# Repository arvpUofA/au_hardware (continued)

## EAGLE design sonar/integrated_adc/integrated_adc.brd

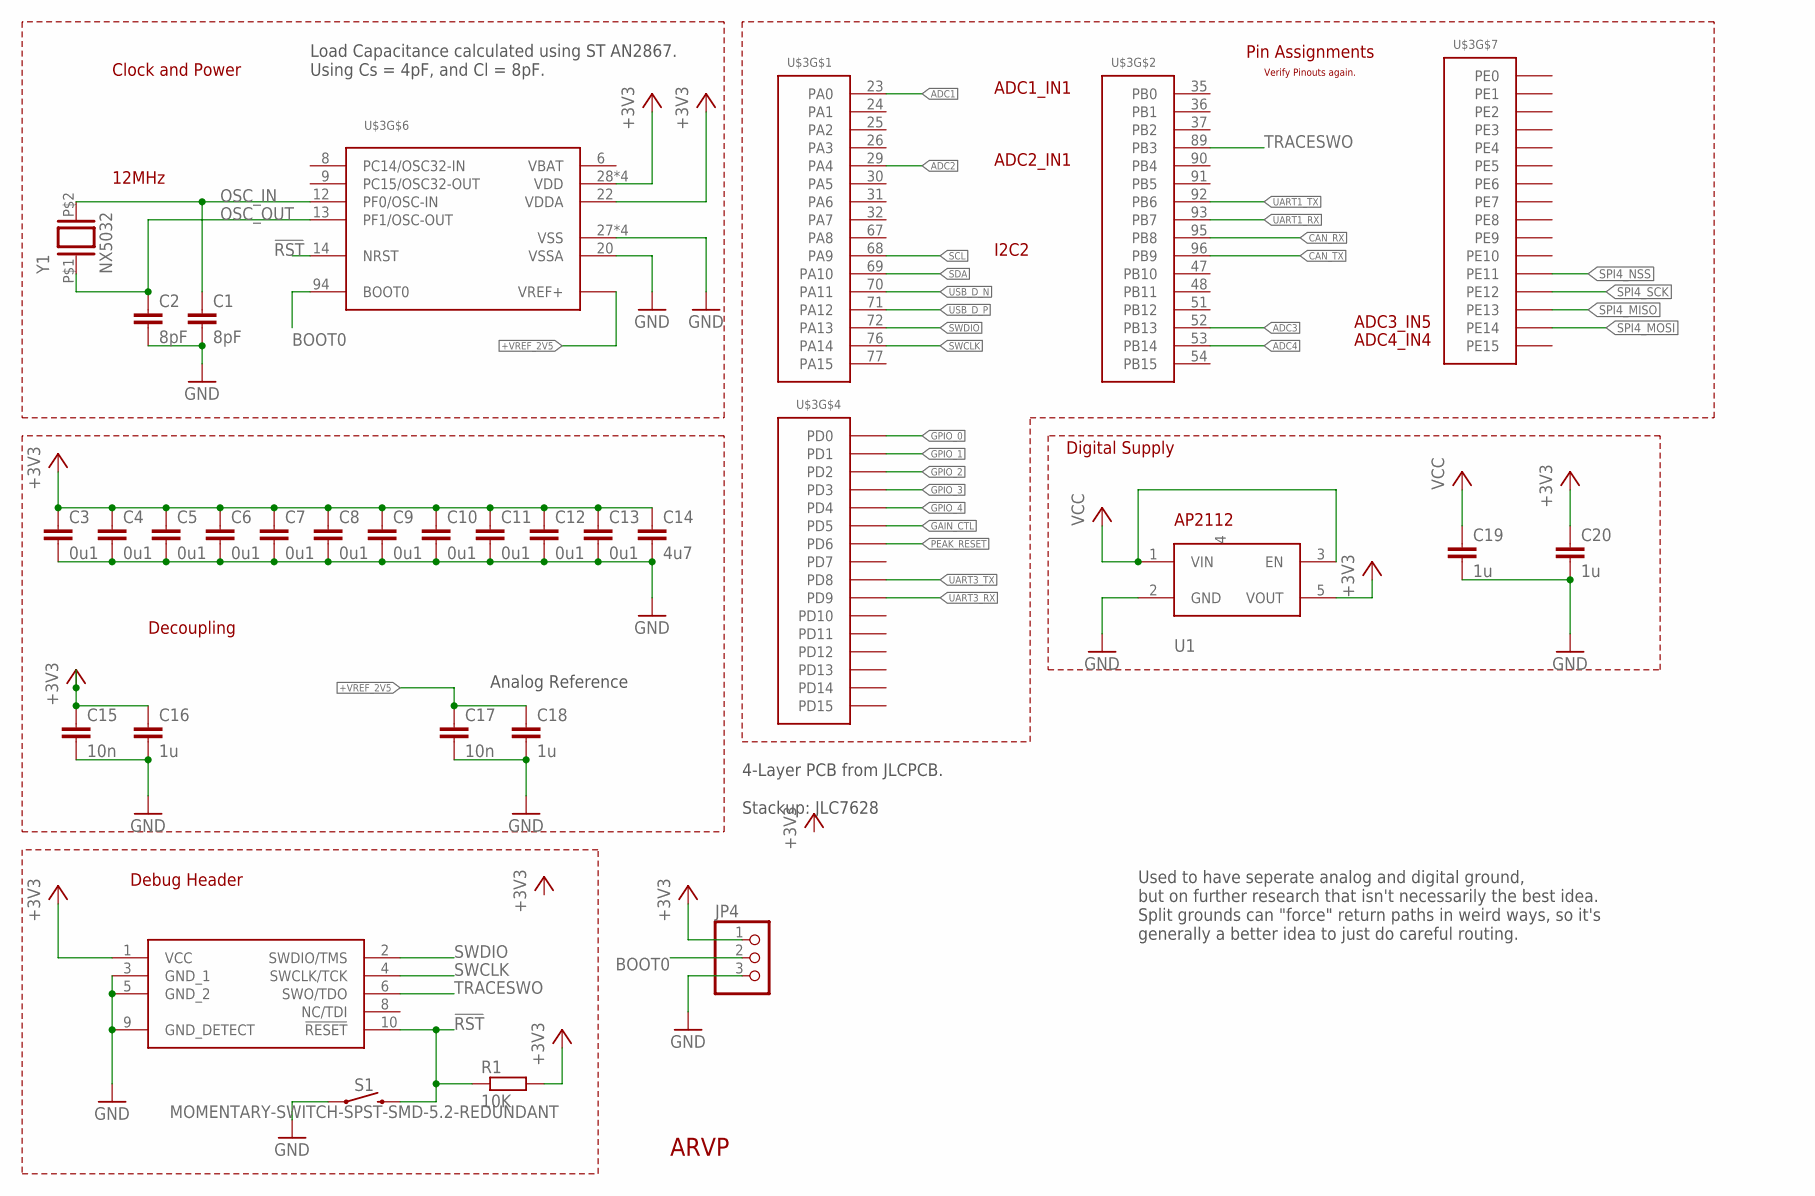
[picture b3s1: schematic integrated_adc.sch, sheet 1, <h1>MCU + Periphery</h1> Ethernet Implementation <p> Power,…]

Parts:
ARVP1: ARVP_LOGO; ARVP
C1, C2: 8pF; C0805
C3, C4, C5, C6, C7, C8, C9, C10, C11, C12, C13: 0u1; C0805
C14: 4u7; C0805
C15, C17: 10n; C0805
C16, C18, C19, C20: 1u; C0805
JP1: CORTEX-M-DBG; FTSH-105-01-F-DV-007
JP4: PINHD-1X3; 1X03
R1: 10K; R0805
S1: MOMENTARY-SWITCH-SPST-SMD-5.2-REDUNDANT; TACTILE_SWITCH_SMD_5.2MM
U1: AP2112K-3.3TRG1; SOT25
U$3: STM32F303VE; LQFP100
Y1: NX5032

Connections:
!RST: JP1.10 (!RESET), R1.1, S1.3 (2), S1.4 (2), U$3.14 (NRST)
+VREF_2V5: C17.1, C18.1, U$3.21 (VREF+); also elsewhere on the board
ADC1: U$3.23 (PA0); also elsewhere on the board
ADC2: U$3.29 (PA4); also elsewhere on the board
ADC3: U$3.52 (PB13); also elsewhere on the board
ADC4: U$3.53 (PB14); also elsewhere on the board
BOOT0: JP4.2, U$3.94 (BOOT0)
CAN_RX: U$3.95 (PB8); also elsewhere on the board
CAN_TX: U$3.96 (PB9); also elsewhere on the board
GAIN_CTL: U$3.86 (PD5); also elsewhere on the board
GND: C1.2, C2.2, C3.2, C4.2, C5.2, C6.2, C7.2, C8.2, C9.2, C10.2, C11.2, C12.2, C13.2, C14.2, C15.2, C16.2, C17.2, C18.2, C19.2, C20.2, JP1.3 (GND_1), JP1.5 (GND_2), JP1.9 (GND_DETECT), JP4.3, S1.1, S1.2 (1), U1.2 (GND), U$3.20 (VSSA), U$3.27 (VSS), U$3.49 (VSS), U$3.74 (VSS), U$3.99 (VSS); also elsewhere on the board
GPIO_0: U$3.81 (PD0); also elsewhere on the board
GPIO_1: U$3.82 (PD1); also elsewhere on the board
GPIO_2: U$3.83 (PD2); also elsewhere on the board
GPIO_3: U$3.84 (PD3); also elsewhere on the board
GPIO_4: U$3.85 (PD4); also elsewhere on the board
OSC_IN: C1.1, U$3.12 (PF0/OSC-IN), Y1.P$2 (2)
OSC_OUT: C2.1, U$3.13 (PF1/OSC-OUT), Y1.P$1 (1)
PEAK_RESET: U$3.87 (PD6); also elsewhere on the board
SCL: U$3.68 (PA9); also elsewhere on the board
SDA: U$3.69 (PA10); also elsewhere on the board
SPI4_MISO: U$3.44 (PE13); also elsewhere on the board
SPI4_MOSI: U$3.45 (PE14); also elsewhere on the board
SPI4_NSS: U$3.42 (PE11); also elsewhere on the board
SPI4_SCK: U$3.43 (PE12); also elsewhere on the board
SWCLK: JP1.4 (SWCLK/TCK), U$3.76 (PA14)
SWDIO: JP1.2 (SWDIO/TMS), U$3.72 (PA13)
TRACESWO: JP1.6 (SWO/TDO), U$3.89 (PB3)
UART1_RX: U$3.93 (PB7)
UART1_TX: U$3.92 (PB6)
UART3_RX: U$3.56 (PD9); also elsewhere on the board
UART3_TX: U$3.55 (PD8); also elsewhere on the board
USB_D_N: U$3.70 (PA11); also elsewhere on the board
USB_D_P: U$3.71 (PA12); also elsewhere on the board
VCC: C19.1, U1.1 (VIN), U1.3 (EN); also elsewhere on the board

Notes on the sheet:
12MHz
ADC1_IN1
ADC2_IN1
ADC3_IN5
ADC4_IN4
Pin Assignments
Decoupling
Clock and Power
Debug Header
Verify Pinouts again.
I2C2
Analog Reference
Digital Supply
Used to have seperate analog and digital ground, but on further research that isn't necessarily the best idea. Split grounds can "force" return paths in weird ways, so it's generally a better idea to just do careful routing.
4-Layer PCB from JLCPCB. Stackup: JLC7628
Load Capacitance calculated using ST AN2867. Using Cs = 4pF, and Cl = 8pF.

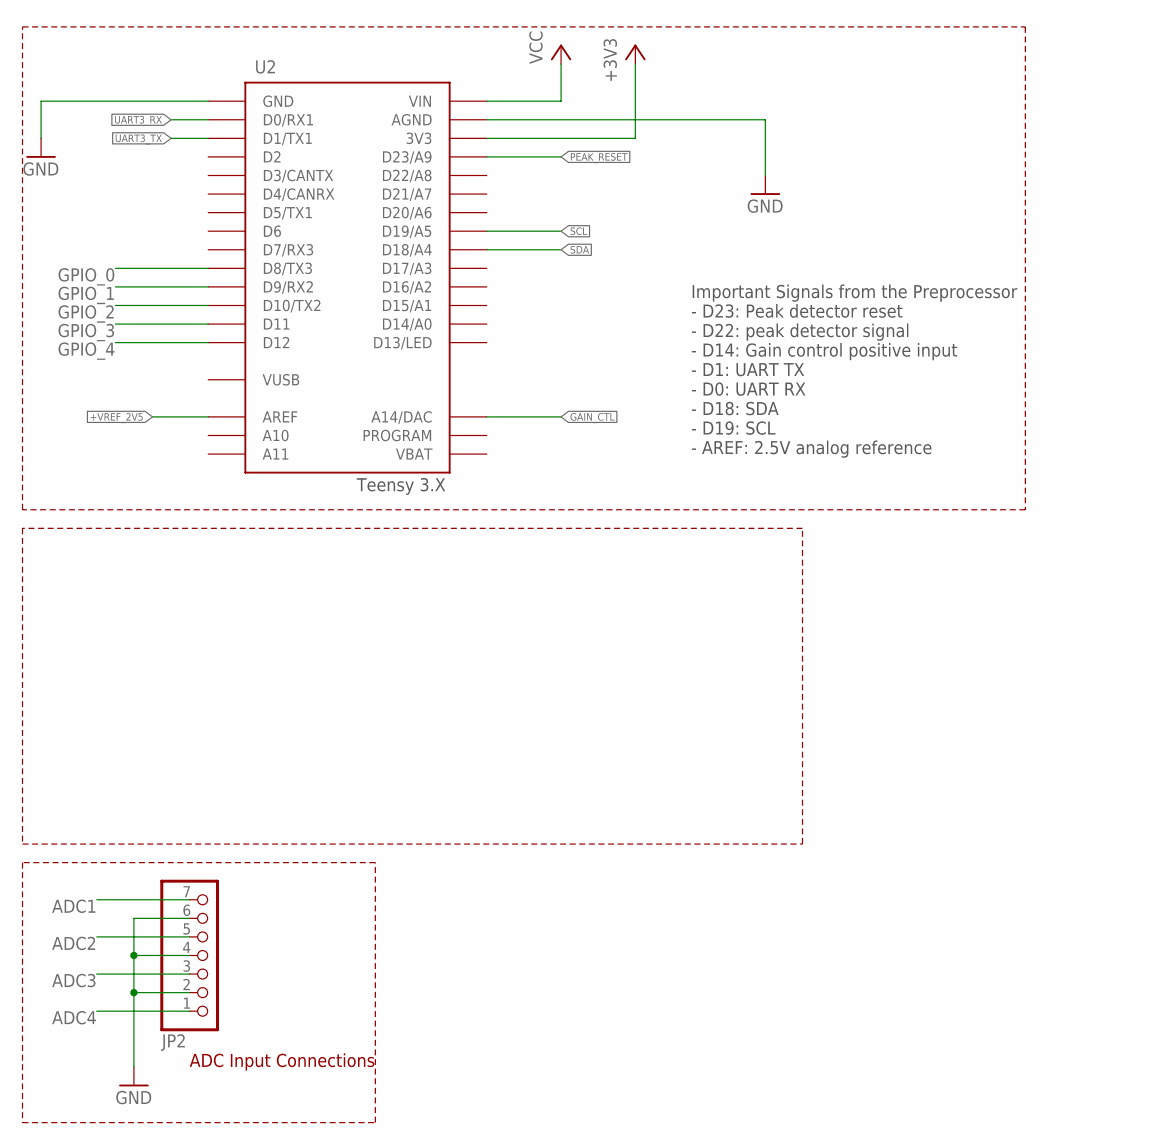
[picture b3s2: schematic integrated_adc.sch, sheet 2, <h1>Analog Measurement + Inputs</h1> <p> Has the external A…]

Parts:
JP2: PINHD-1X7/90; 1X07/90
U2: TEENSY_3.X_PINOUT

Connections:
+VREF_2V5: U2.AREF; also elsewhere on the board
ADC1: JP2.7; also elsewhere on the board
ADC2: JP2.5; also elsewhere on the board
ADC3: JP2.3; also elsewhere on the board
ADC4: JP2.1; also elsewhere on the board
GAIN_CTL: U2.A14 (A14/DAC); also elsewhere on the board
GND: JP2.2, JP2.4, JP2.6, U2.AGND, U2.GND_1 (GND), U2.GND_2 (GND); also elsewhere on the board
GPIO_0: U2.D8 (D8/TX3); also elsewhere on the board
GPIO_1: U2.D9 (D9/RX2); also elsewhere on the board
GPIO_2: U2.D10 (D10/TX2); also elsewhere on the board
GPIO_3: U2.D11; also elsewhere on the board
GPIO_4: U2.D12; also elsewhere on the board
PEAK_RESET: U2.D23 (D23/A9); also elsewhere on the board
SCL: U2.D19 (D19/A5); also elsewhere on the board
SDA: U2.D18 (D18/A4); also elsewhere on the board
UART3_RX: U2.D0 (D0/RX1); also elsewhere on the board
UART3_TX: U2.D1 (D1/TX1); also elsewhere on the board
VCC: U2.VIN; also elsewhere on the board
VUSB: U2.VUSB

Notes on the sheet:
ADC Input Connections
Important Signals from the Preprocessor - D23: Peak detector reset - D22: peak detector signal - D14: Gain control positive input - D1: UART TX - D0: UART RX - D18: SDA - D19: SCL - AREF: 2.5V analog reference

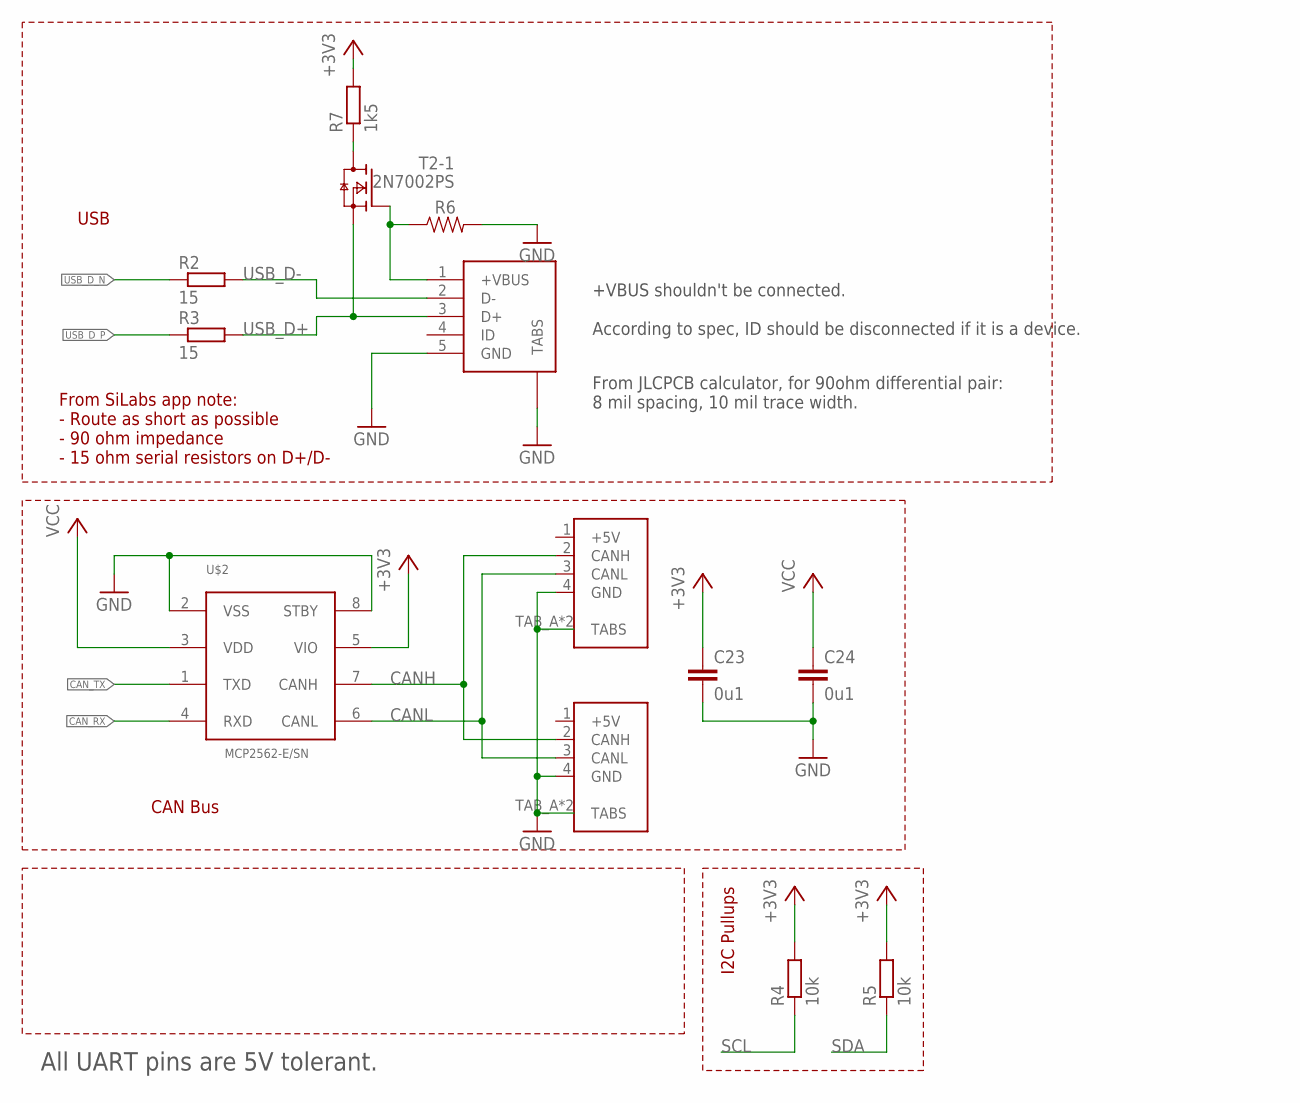
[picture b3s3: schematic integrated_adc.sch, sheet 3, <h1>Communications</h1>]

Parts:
C23, C24: 0u1; C0805
CON1, CON2: UAVCAN_MICRO; SM04B-GHS-TB
R2, R3: 15; R0805
R4, R5: 10k; R0805
R6: 1206
R7: 1k5; R0805
T2: 2N7002PS; SOT363
U$2: MCP2562-E/SN; SOIC8
U$4: AMPHENOL_MICROB-USB; AMPHENOL_MICROB_SMD

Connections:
CANH: CON1.2 (CANH), CON2.2 (CANH), U$2.7 (CANH)
CANL: CON1.3 (CANL), CON2.3 (CANL), U$2.6 (CANL)
CAN_RX: U$2.4 (RXD); also elsewhere on the board
CAN_TX: U$2.1 (TXD); also elsewhere on the board
GND: C23.2, C24.2, CON1.4 (GND), CON1.TAB_A (TABS), CON1.TAB_B (TABS), CON2.4 (GND), CON2.TAB_A (TABS), CON2.TAB_B (TABS), R6.2, U$2.2 (VSS), U$2.8 (STBY), U$4.5 (GND), U$4.TAB1 (TABS), U$4.TAB2 (TABS), U$4.TAB3 (TABS), U$4.TAB4 (TABS); also elsewhere on the board
unnamed: R6.1, T2.2 (G), U$4.1 (+VBUS)
unnamed: R7.1, T2.6 (D)
SCL: R4.1; also elsewhere on the board
SDA: R5.1; also elsewhere on the board
USB_D+: R3.2, T2.1 (S), U$4.3 (D+)
USB_D-: R2.2, U$4.2 (D-)
USB_D_N: R2.1; also elsewhere on the board
USB_D_P: R3.1; also elsewhere on the board
VCC: C24.1, U$2.3 (VDD); also elsewhere on the board

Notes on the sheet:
From SiLabs app note: - Route as short as possible - 90 ohm impedance - 15 ohm serial resistors on D+/D-
+VBUS shouldn't be connected. According to spec, ID should be disconnected if it is a device.
CAN Bus
USB
All UART pins are 5V tolerant.
From JLCPCB calculator, for 90ohm differential pair: 8 mil spacing, 10 mil trace width.
I2C Pullups

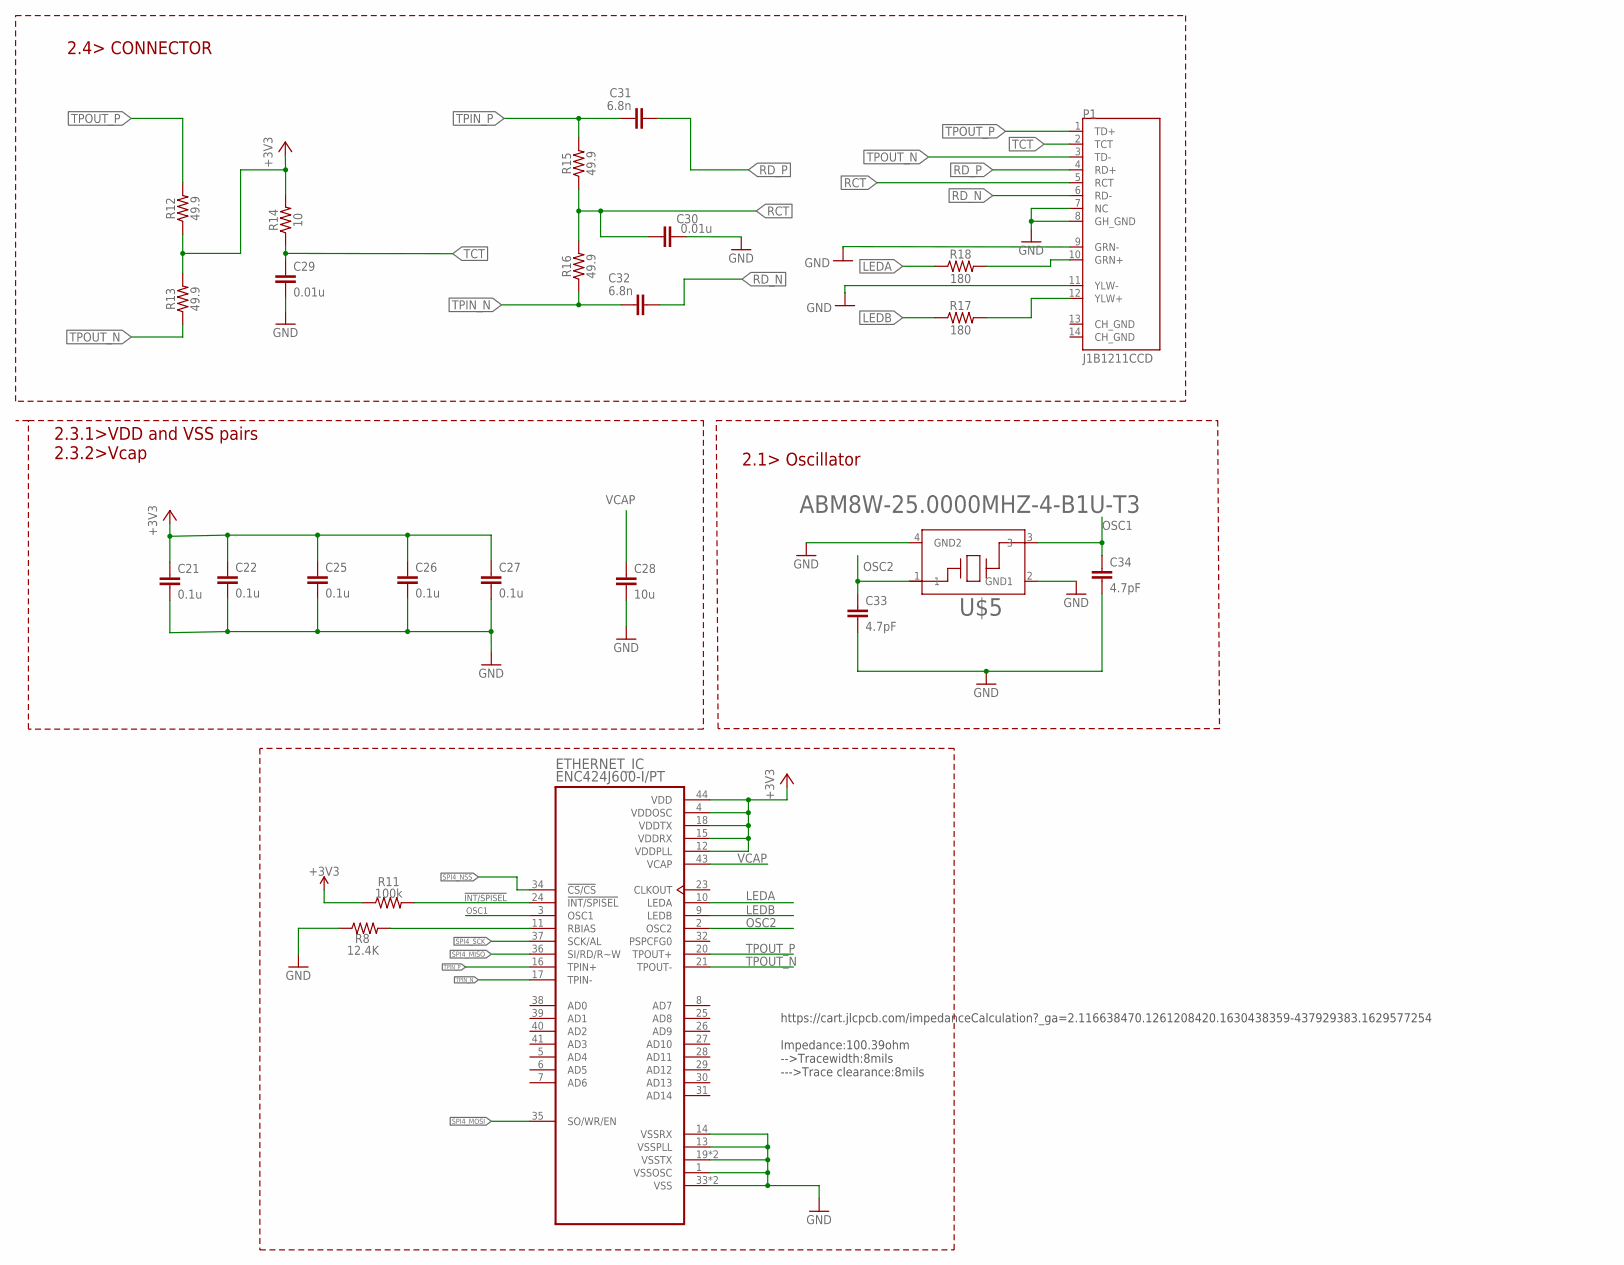
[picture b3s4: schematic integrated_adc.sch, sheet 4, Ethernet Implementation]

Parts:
C21, C22, C25, C26, C27: 0.1u; C0402
C28: 10u; C0402
C29, C30: 0.01u; C0402
C31, C32: 6.8n; C0402
C33, C34: 4.7pF; C0402
ETHERNET_IC: ENC424J600-I/PT; QFP80P1200X1200X120-44N
P1: J1B1211CCD
R8: 12.4K; 0603
R11: 100k; 0603
R12, R13, R15, R16: 49.9; 0603
R14: 10; 0603
R17, R18: 180; RESC1608X55N
U$5: ABM8W-25.0000MHZ-4-B1U-T3; XTAL_ABM8W-25.0000MHZ-4-B1U-T3

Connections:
!INT/SPISEL!: ETHERNET_IC.24 (!INT/SPISEL), R11.2
GND: C21.2, C22.2, C25.2, C26.2, C27.2, C28.2, C29.2, C30.2, C33.2, C34.2, ETHERNET_IC.1 (VSSOSC), ETHERNET_IC.13 (VSSPLL), ETHERNET_IC.14 (VSSRX), ETHERNET_IC.19 (VSSTX), ETHERNET_IC.22 (VSSTX), ETHERNET_IC.33 (VSS), ETHERNET_IC.42 (VSS), P1.7 (NC), P1.8 (GH_GND), P1.9 (GRN-), P1.11 (YLW-), R8.1, U$5.2 (GND1), U$5.4 (GND2); also elsewhere on the board
LEDA: ETHERNET_IC.10 (LEDA), R18.1
LEDB: ETHERNET_IC.9 (LEDB), R17.1
unnamed: P1.10 (GRN+), R18.2
unnamed: P1.12 (YLW+), R17.2
OSC1: C34.1, ETHERNET_IC.3 (OSC1), U$5.3
OSC2: C33.1, ETHERNET_IC.2 (OSC2), U$5.1
RBIAS: ETHERNET_IC.11 (RBIAS), R8.2
RCT: C30.1, P1.5 (RCT), R15.1, R16.2
RD_N: C32.1, P1.6 (RD-)
RD_P: C31.2, P1.4 (RD+)
SPI4_MISO: ETHERNET_IC.36 (SI/RD/R~W); also elsewhere on the board
SPI4_MOSI: ETHERNET_IC.35 (SO/WR/EN); also elsewhere on the board
SPI4_NSS: ETHERNET_IC.34 (!CS/CS); also elsewhere on the board
SPI4_SCK: ETHERNET_IC.37 (SCK/AL); also elsewhere on the board
TCT: C29.1, P1.2 (TCT), R14.1
TPIN_N: C32.2, ETHERNET_IC.17 (TPIN-), R16.1
TPIN_P: C31.1, ETHERNET_IC.16 (TPIN+), R15.2
TPOUT_N: ETHERNET_IC.21 (TPOUT-), P1.3 (TD-), R13.1
TPOUT_P: ETHERNET_IC.20 (TPOUT+), P1.1 (TD+), R12.2
VCAP: C28.1, ETHERNET_IC.43 (VCAP)

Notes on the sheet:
2.1> Oscillator
2.3.1>VDD and VSS pairs 2.3.2>Vcap
2.4> CONNECTOR
https://cart.jlcpcb.com/impedanceCalculation?_ga=2.116638470.1261208420.1630438359-437929383.1629577254 Impedance:100.39ohm -->Tracewidth:8mils --->Trace clearance:8mils

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
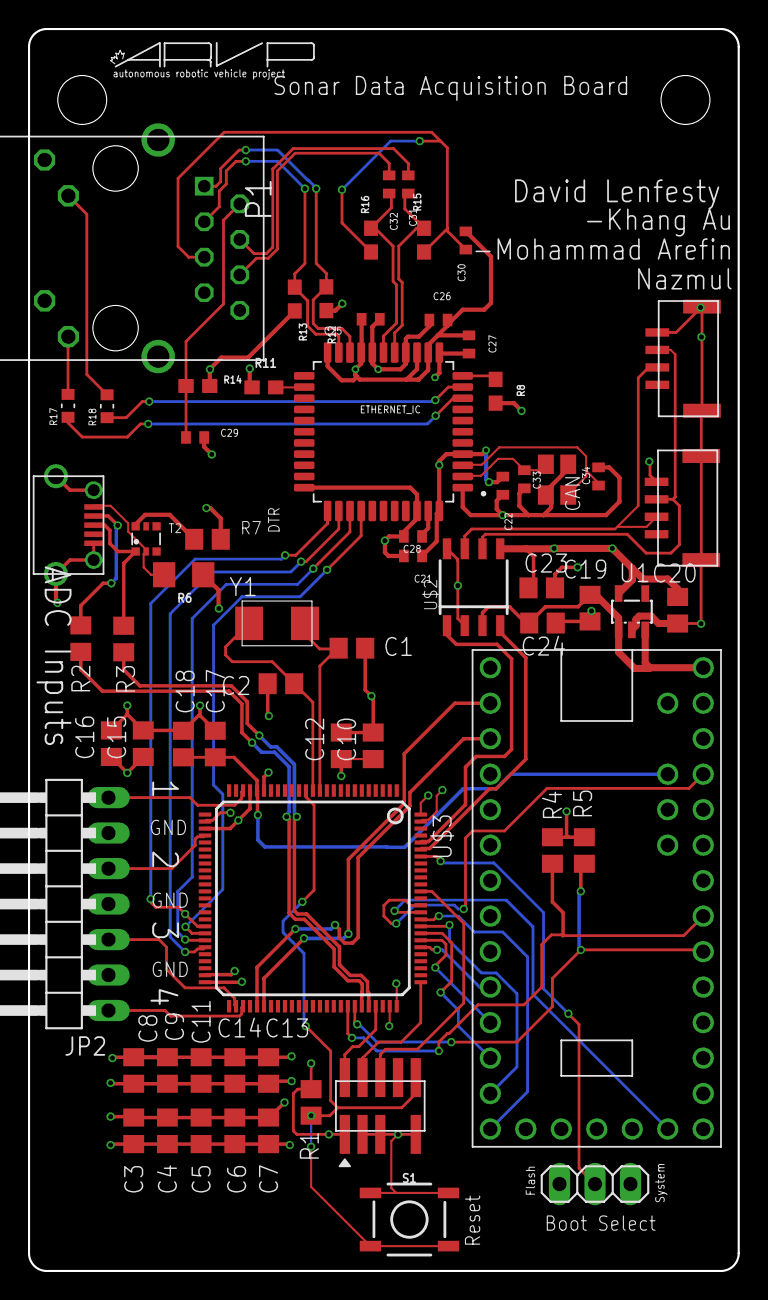
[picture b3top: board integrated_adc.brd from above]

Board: 4 copper layers, 50.8 x 88.9 mm, 67 parts (0 on the bottom side), 57 nets.

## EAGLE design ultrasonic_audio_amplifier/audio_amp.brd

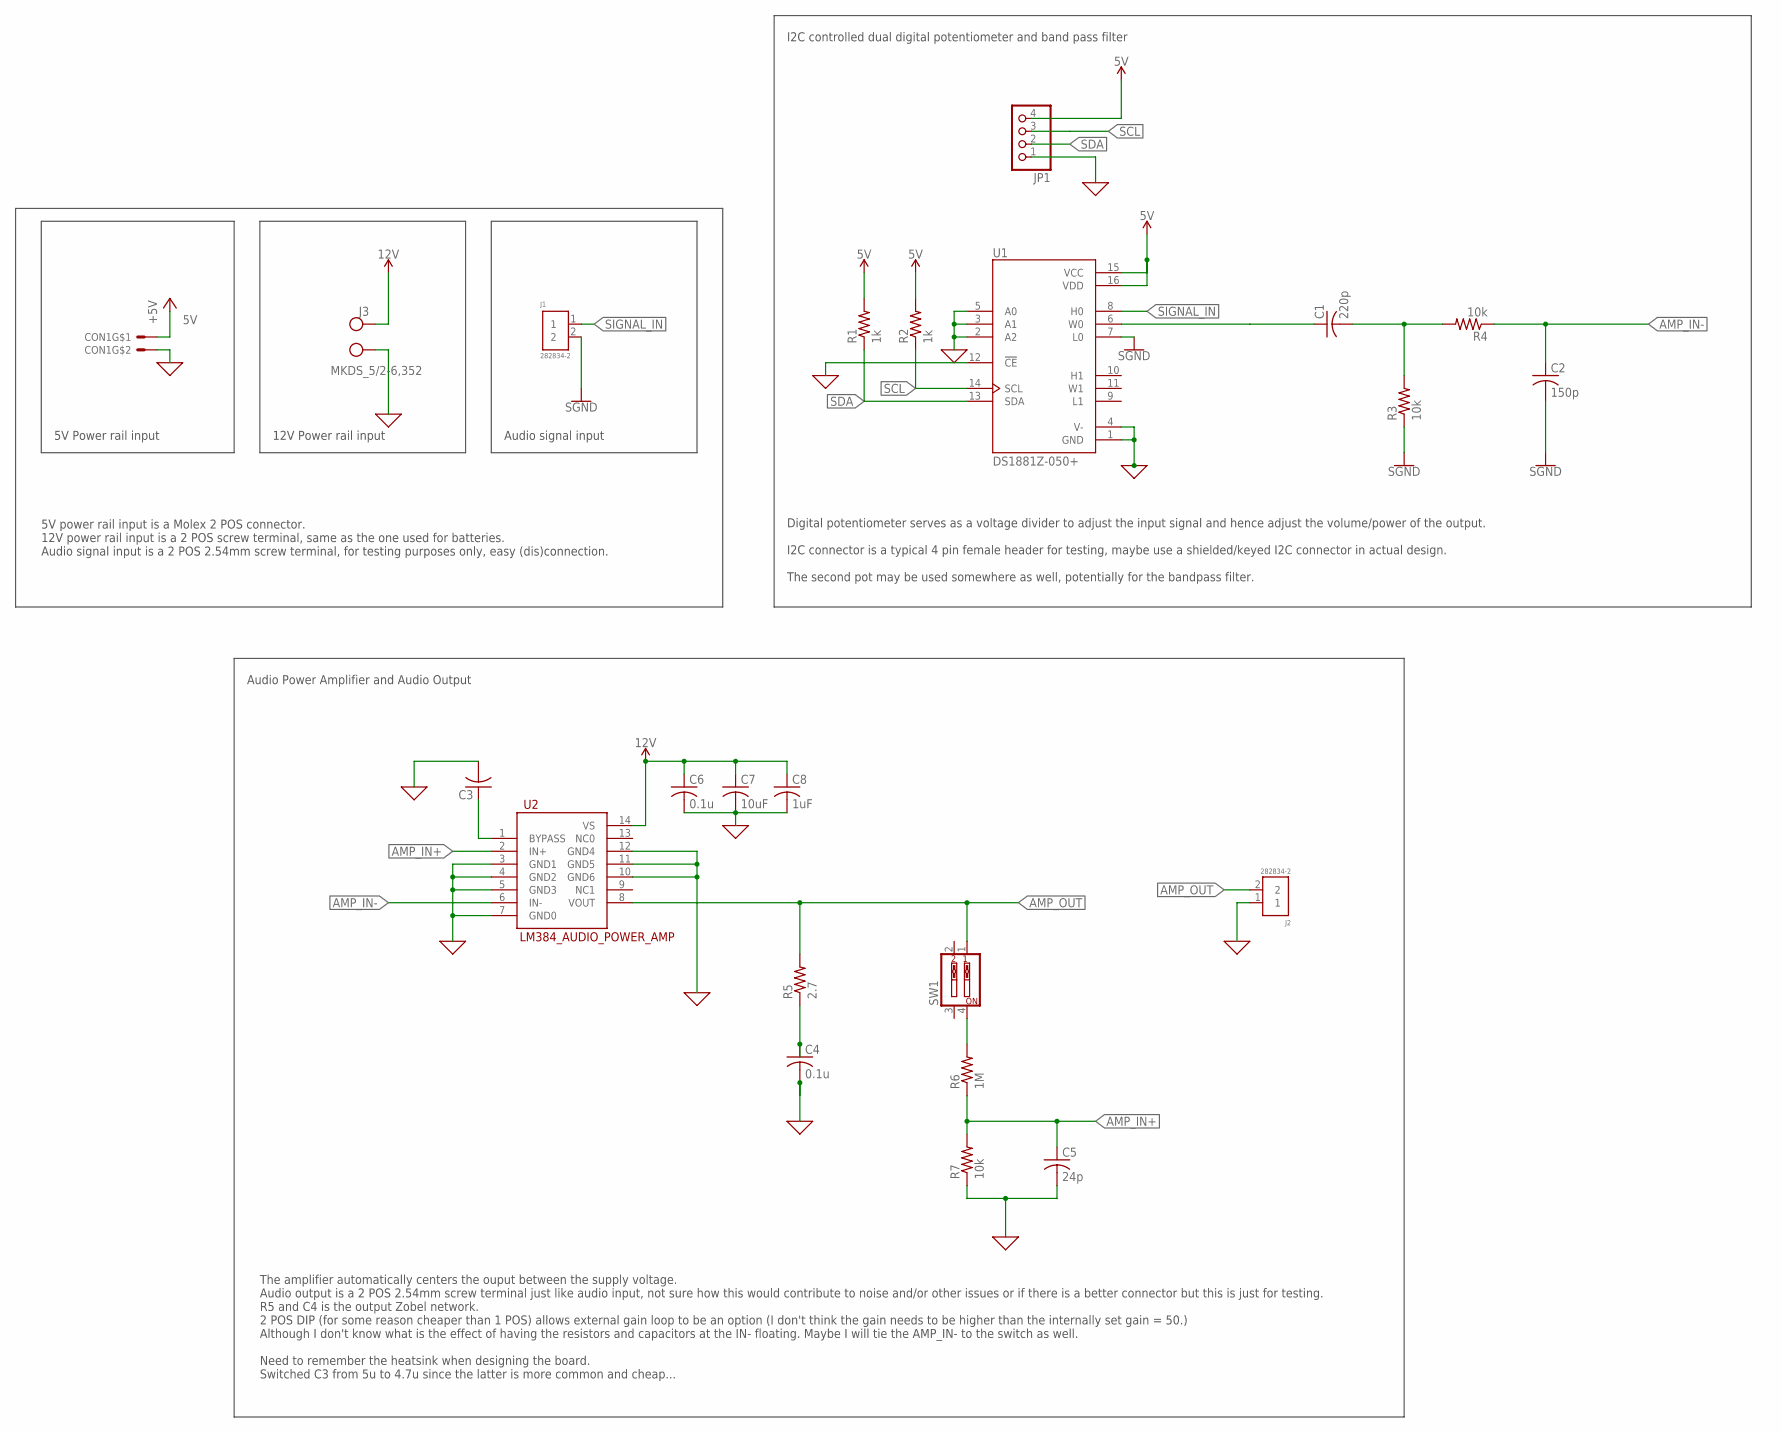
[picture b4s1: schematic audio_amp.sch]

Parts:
C1: 220p; CAP7.2MM*4.5MM
C2: 150p; CAP7.2MM*4.5MM
C3: C-USC0805; C0805
C4, C6: 0.1u; C0805
C5: 24p; C0805
C7: 10uF; C1206
C8: 1uF; C1206
CON1: MOLEX_5566-2; 5566-2
J1, J2: 282834-2; 2P_SCREW_TERM
J3: MKDS_5/2-6,352; MKDS_5/2-6,35
JP1: PINHD-1X4; 1X04
R1, R2: 1k; R1206
R3, R4, R7: 10k; R0805
R5: 2.7; R1206
R6: 1M; R0805
SW1: SW_DIP-2; EDG-02
U1: DS1881Z-050+; 16-SOIC
U2: LM384_AUDIO_POWER_AMP; DIP14

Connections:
0: C3.2, C4.2, C5.2, C6.2, C7.2, C8.2, CON1.2, J2.1, J3.1 (KL), JP1.1, R7.1, U1.1 (GND), U1.2 (A2), U1.3 (A1), U1.4 (V-), U1.5 (A0), U1.12 (!CE), U2.3 (GND1), U2.4 (GND2), U2.5 (GND3), U2.7 (GND0), U2.10 (GND6), U2.11 (GND5), U2.12 (GND4)
5V: CON1.1, JP1.4, R1.2, R2.2, U1.15 (VCC), U1.16 (VDD)
12V: C6.1, C7.1, C8.1, J3.2 (KL1), U2.14 (VS)
AMP_IN+: C5.1, R6.1, R7.2, U2.2 (IN+)
AMP_IN-: C2.P$1 (1), R4.1, U2.6 (IN-)
AMP_OUT: J2.2, R5.2, SW1.1, U2.8 (VOUT)
GND: C2.P$2 (2), J1.2, R3.1, U1.7 (L0)
unnamed: C1.P$2 (2), R3.2, R4.2
unnamed: C3.1, U2.1 (BYPASS)
unnamed: C4.1, R5.1
unnamed: R6.2, SW1.4
SCL: JP1.3, R2.1, U1.14 (SCL)
SDA: JP1.2, R1.1, U1.13 (SDA)
SIGNAL_IN: J1.1, U1.8 (H0)
SIGNAL_OUT: C1.P$1 (1), U1.6 (W0)

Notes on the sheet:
Audio signal input
12V Power rail input
5V Power rail input
5V power rail input is a Molex 2 POS connector. 12V power rail input is a 2 POS screw terminal, same as the one used for batteries. Audio signal input is a 2 POS 2.54mm screw terminal, for testing purposes only, easy (dis)connection.
I2C controlled dual digital potentiometer and band pass filter
Digital potentiometer serves as a voltage divider to adjust the input signal and hence adjust the volume/power of the output. I2C connector is a typical 4 pin female header for testing, maybe use a shielded/keyed I2C connector in actual design. The second pot may be used somewhere as well, potentia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
Audio Power Amplifier and Audio Output
The amplifier automatically centers the ouput between the supply voltage. Audio output is a 2 POS 2.54mm screw terminal just like audio input, not sure how this would contribute to noise and/or other issues or if there is a better connector but this is just for testing. R5 and C4 is the output Zobe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

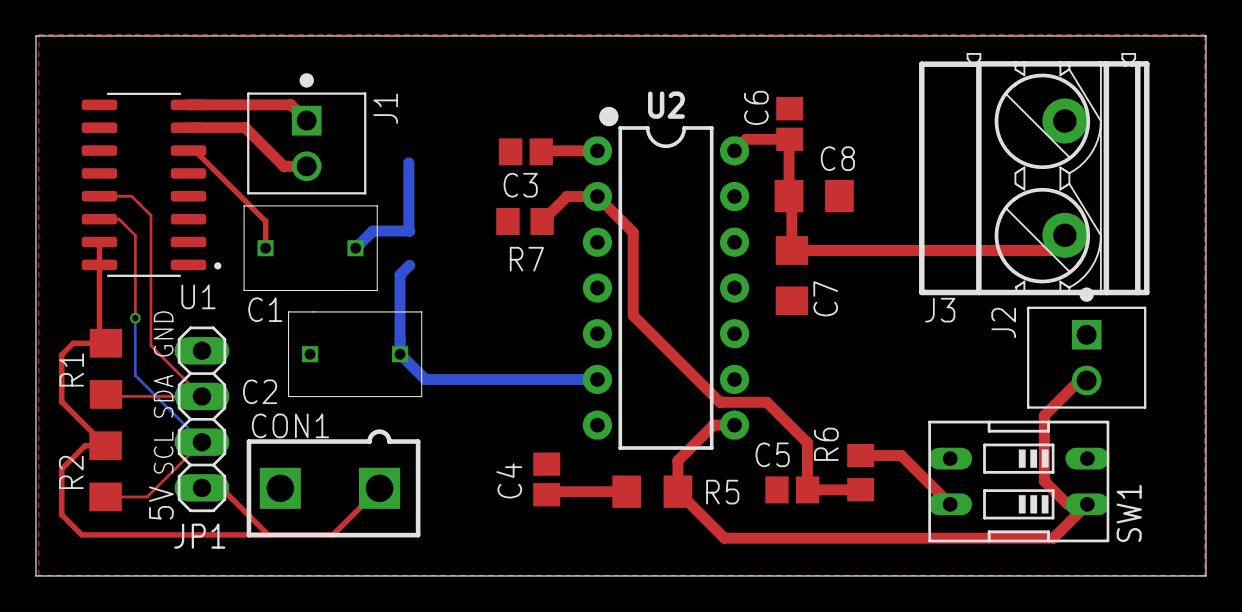
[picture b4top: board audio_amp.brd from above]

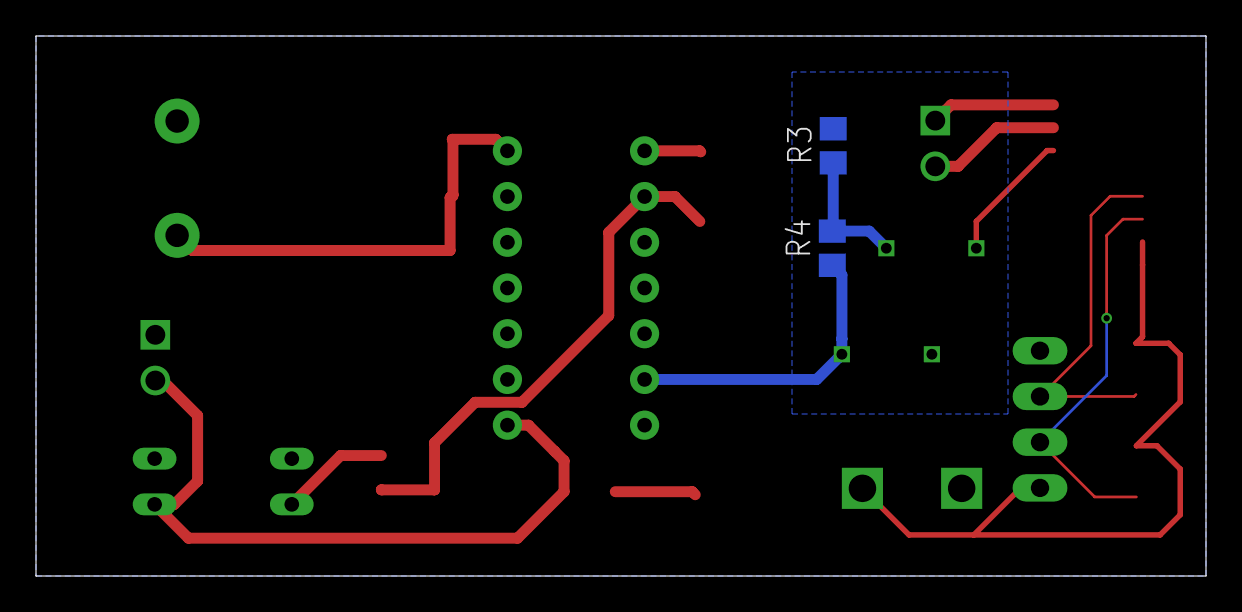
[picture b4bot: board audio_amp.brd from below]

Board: 2 copper layers, 65.0 x 30.0 mm, 23 parts (2 on the bottom side), 15 nets.

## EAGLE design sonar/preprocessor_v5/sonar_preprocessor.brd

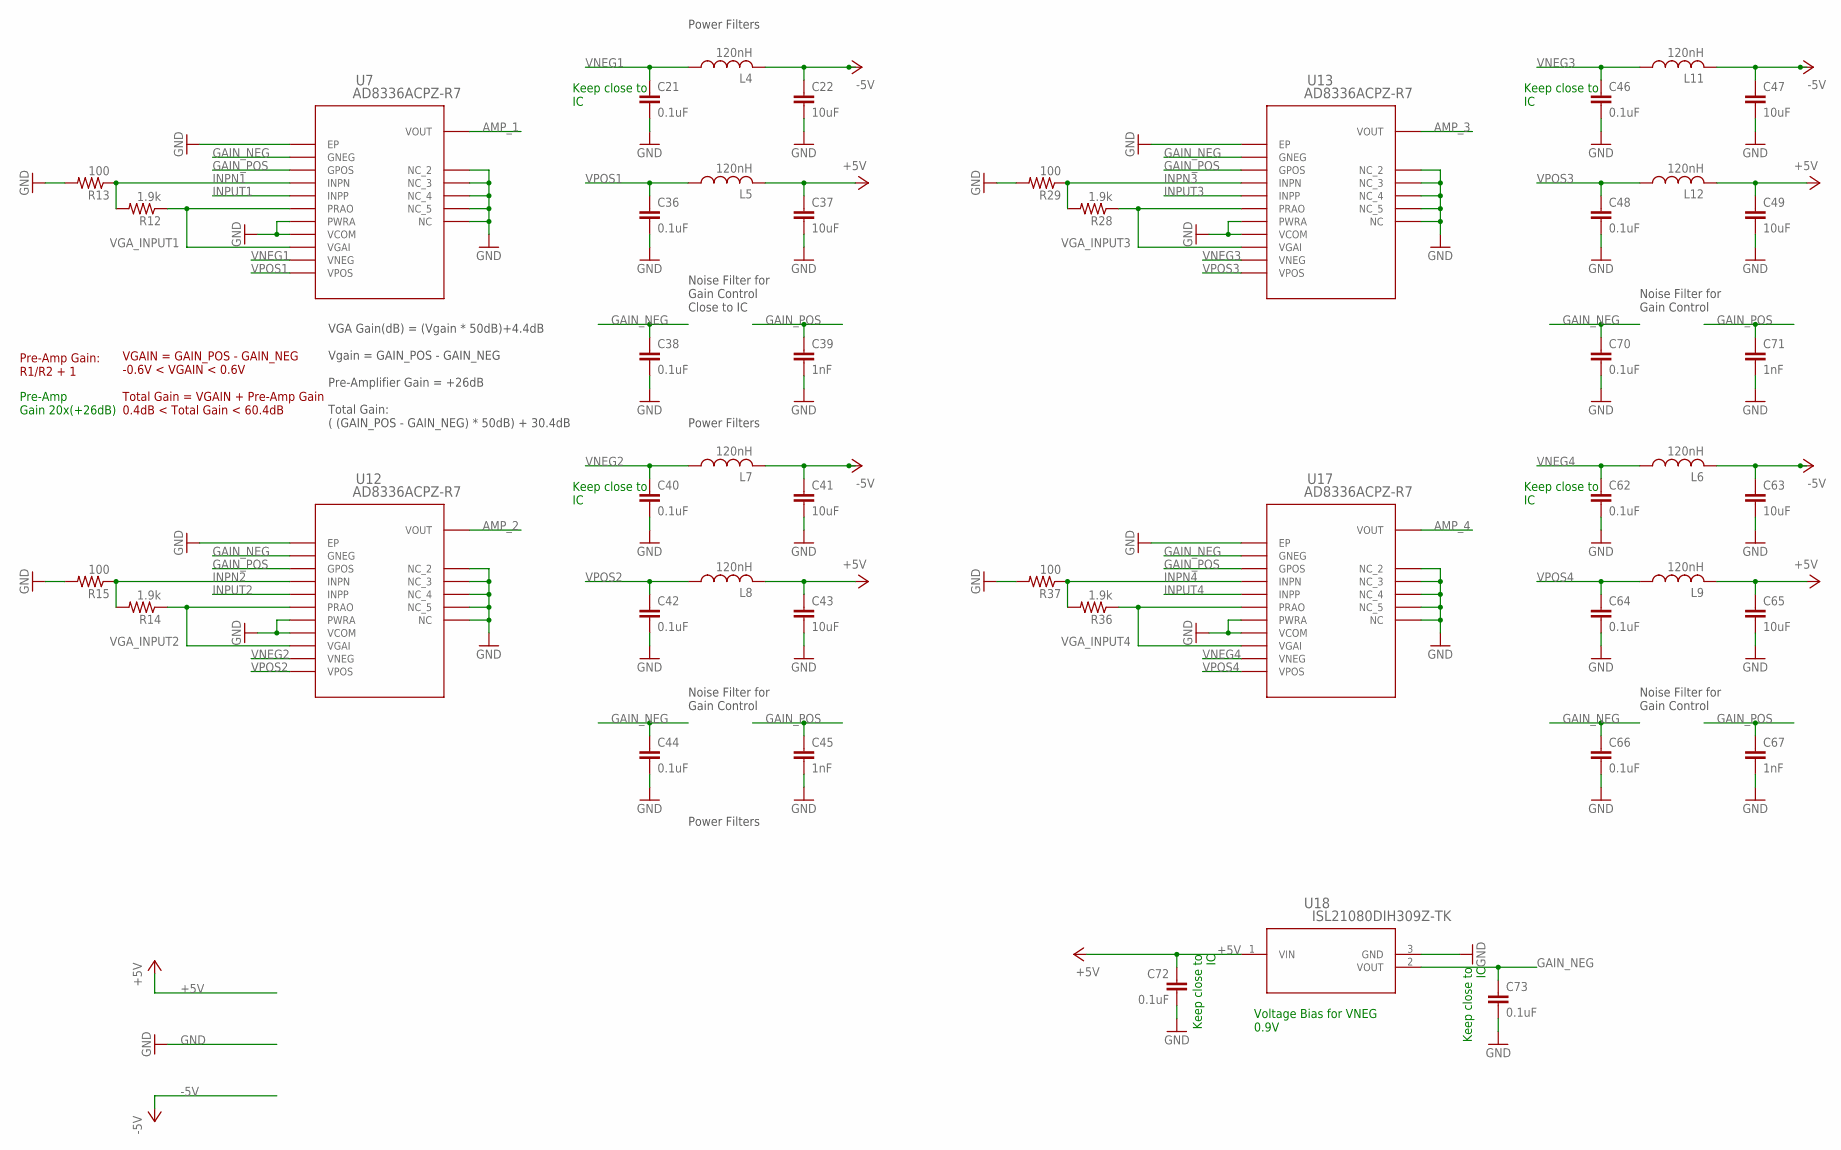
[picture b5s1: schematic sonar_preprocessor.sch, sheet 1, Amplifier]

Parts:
C21, C36, C38, C40, C42, C44, C46, C48, C62, C64, C66, C70, C72, C73: 0.1uF; C0603
C22, C37, C41, C43, C47, C49, C63, C65: 10uF; C1206
C39, C45, C67, C71: 1nF; C0603
L4, L5, L6, L7, L8, L9, L11, L12: 120nH; L3225P
R12, R14, R28, R36: 1.9k; R0603
R13, R15, R29, R37: 100; R0603
U7, U12, U13, U17: AD8336ACPZ-R7; CP_16_4
U18: ISL21080DIH309Z-TK; P3_064

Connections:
+5V: C37.1, C43.1, C49.1, C65.1, C72.1, L5.2, L8.2, L9.2, L12.2, U18.1 (VIN); also elsewhere on the board
-5V: C22.1, C41.1, C47.1, C63.1, L4.2, L6.2, L7.2, L11.2; also elsewhere on the board
AMP_1: U7.VOUT; also elsewhere on the board
AMP_2: U12.VOUT; also elsewhere on the board
AMP_3: U13.VOUT; also elsewhere on the board
AMP_4: U17.VOUT; also elsewhere on the board
GAIN_NEG: C38.1, C44.1, C66.1, C70.1, C73.1, U7.GNEG, U12.GNEG, U13.GNEG, U17.GNEG, U18.2 (VOUT)
GAIN_POS: C39.1, C45.1, C67.1, C71.1, U7.GPOS, U12.GPOS, U13.GPOS, U17.GPOS; also elsewhere on the board
GND: C21.2, C22.2, C36.2, C37.2, C38.2, C39.2, C40.2, C41.2, C42.2, C43.2, C44.2, C45.2, C46.2, C47.2, C48.2, C49.2, C62.2, C63.2, C64.2, C65.2, C66.2, C67.2, C70.2, C71.2, C72.2, C73.2, R13.2, R15.2, R29.2, R37.2, U7.GND1 (EP), U7.NC, U7.NC1 (NC_2), U7.NC2 (NC_3), U7.NC3 (NC_4), U7.NC4 (NC_5), U7.PWRA, U7.VCOM, U12.GND1 (EP), U12.NC, U12.NC1 (NC_2), U12.NC2 (NC_3), U12.NC3 (NC_4), U12.NC4 (NC_5), U12.PWRA, U12.VCOM, U13.GND1 (EP), U13.NC, U13.NC1 (NC_2), U13.NC2 (NC_3), U13.NC3 (NC_4), U13.NC4 (NC_5), U13.PWRA, U13.VCOM, U17.GND1 (EP), U17.NC, U17.NC1 (NC_2), U17.NC2 (NC_3), U17.NC3 (NC_4), U17.NC4 (NC_5), U17.PWRA, U17.VCOM, U18.3 (GND); also elsewhere on the board
INPN1: R12.2, R13.1, U7.INPN
INPN2: R14.2, R15.1, U12.INPN
INPN3: R28.2, R29.1, U13.INPN
INPN4: R36.2, R37.1, U17.INPN
INPUT1: U7.INPP; also elsewhere on the board
INPUT2: U12.INPP; also elsewhere on the board
VGA_INPUT1: R12.1, U7.PRAO, U7.VGAI
VGA_INPUT2: R14.1, U12.PRAO, U12.VGAI
VGA_INPUT3: R28.1, U13.PRAO, U13.VGAI
VGA_INPUT4: R36.1, U17.PRAO, U17.VGAI
VNEG1: C21.1, L4.1, U7.VNEG
VNEG2: C40.1, L7.1, U12.VNEG
VNEG3: C46.1, L11.1, U13.VNEG
VNEG4: C62.1, L6.1, U17.VNEG
VPOS1: C36.1, L5.1, U7.VPOS
VPOS2: C42.1, L8.1, U12.VPOS
VPOS3: C48.1, L12.1, U13.VPOS
VPOS4: C64.1, L9.1, U17.VPOS

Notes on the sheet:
Pre-Amp Gain 20x(+26dB)
Power Filters
Keep close to IC
Noise Filter for Gain Control Close to IC
Pre-Amp Gain: R1/R2 + 1
VGA Gain(dB) = (Vgain * 50dB)+4.4dB Vgain = GAIN_POS - GAIN_NEG Pre-Amplifier Gain = +26dB Total Gain: ( (GAIN_POS - GAIN_NEG) * 50dB) + 30.4dB
VGAIN = GAIN_POS - GAIN_NEG -0.6V < VGAIN < 0.6V Total Gain = VGAIN + Pre-Amp Gain 0.4dB < Total Gain < 60.4dB
Noise Filter for Gain Control
Voltage Bias for VNEG 0.9V
